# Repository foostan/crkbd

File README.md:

# Corne keyboard

The Corne keyboard is a split keyboard with 3x6 column staggered keys
and 3 thumb keys, based on [Helix](https://github.com/MakotoKurauchi/helix).
Crkbd stands for Corne Keyboard.

## Latest versions
- corne-cherry: for Cherry MX compatible switches

  - v4 Hotswappable ([JP](docs/corne-cherry/v4/buildguide_jp.md)/[EN](docs/corne-cherry/v4/buildguide_en.md))
  - v4 Soldering (will be released)
- corne-chocolate: for Kailh choc v1 and v2 switches
  - v4 Hotswappable ([JP](docs/corne-chocolate/v4/buildguide_jp.md)/[EN](docs/corne-chocolate/v4/buildguide_en.md)):
  - v4 Soldering (will be released)

## Old versions

- corne-classic: for Cherry MX compatible switches 
  - v1 Soldering: ([JP](docs/corne-classic/buildguide_jp.md)/[EN](docs/corne-classic/buildguide_en.md))
- corne-cherry: for Cherry MX compatible switches
  - v2 Hotswappable: ([JP](docs/corne-cherry/v2/buildguide_jp.md)/[EN](docs/corne-cherry/v2/buildguide_en.md))
  - v2 Hotswappable tilting version: ([tilting, JP](docs/corne-cherry/v2/buildguide_tilting_tenting_plate_jp.md)/[tilting, EN](docs/corne-cherry/v2/buildguide_tilting_tenting_plate_en.md)):
  - v3 Hotswappable: ([JP](docs/corne-cherry/v3/buildguide_jp.md)/[EN](docs/corne-cherry/v3/buildguide_en.md))
- corne-chocolate: for Kailh choc v1 switches
  - v2 Hotswappable: ([JP](docs/corne-chocolate/v2/buildguide_jp.md)/[EN](docs/corne-chocolate/v2/buildguide_en.md)):
- corne-light: for easy build with a simple PCB
  - v1 Soldering: ([JP](docs/corne-light/v1/buildguide_jp.md)/[EN](docs/corne-light/v1/buildguide_en.md)):
  - v2 Soldering: ([JP](docs/corne-light/v2/buildguide_low_edition_jp.md)/[EN](docs/corne-light/v2/buildguide_low_edition_en.md)):

## Notice
There are currently reports of a bug in v4.* caused by electromagnetic interference. Depending on the environment, one or both of the left and right keyboards may stop working. It is known that this is often caused by EMI emitted by mobile phones. If you experience this kind of problem, reconnect the USB, move the EMI-generating device (probably a mobile phone) more than 30 cm away from the keyboard, and observe the situation.

For more details, please see this issue. We look forward to receiving any new information.
https://github.com/foostan/crkbd/issues/265

## Images

### Cherry

### Chocolate

### Drawing

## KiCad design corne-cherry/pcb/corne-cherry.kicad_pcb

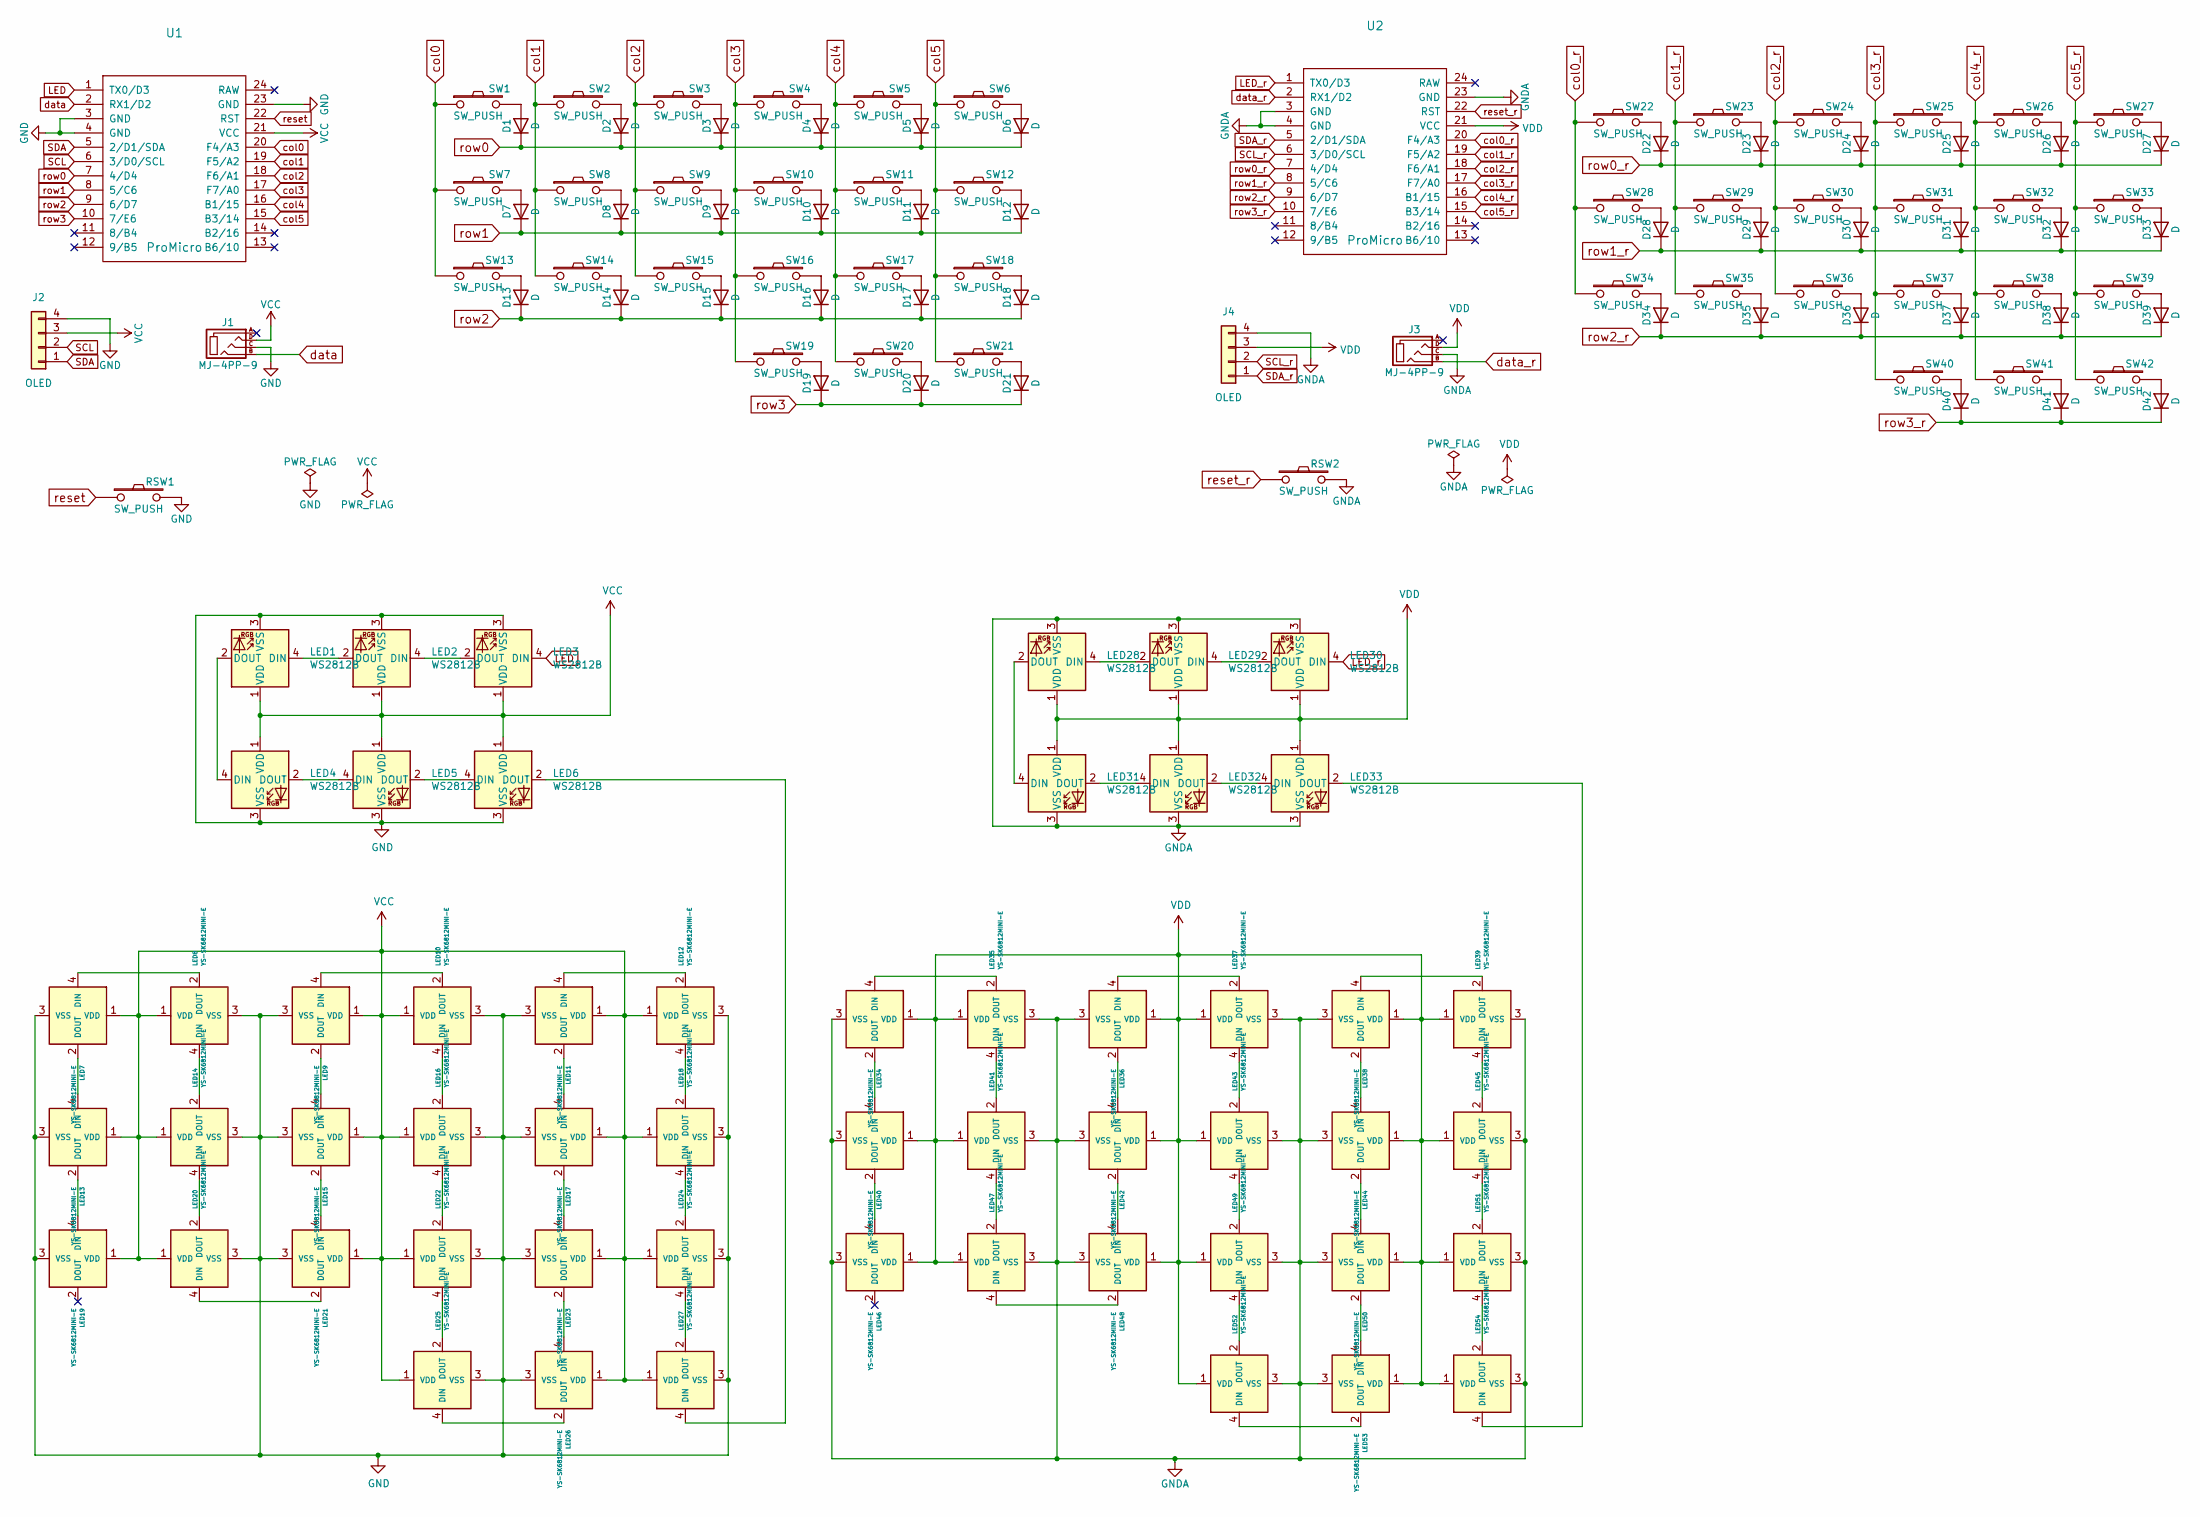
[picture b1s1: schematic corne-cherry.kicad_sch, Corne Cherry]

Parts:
D1, D2, D3, D4, D5, D6, D7, D8, D9, D10, D11, D12, D13, D14, D15, D16, D17, D18, D19, D20, D21, D22, D23, D24, D25, D26, D27, D28, D29, D30, D31, D32, D33, D34, D35, D36, D37, D38, D39, D40, D41, D42: D; D3_SMD_v2
J1, J3: MJ-4PP-9; MJ-4PP-9_1side
J2, J4: OLED; OLED_1side
LED1, LED2, LED3, LED4, LED5, LED6, LED28, LED29, LED30, LED31, LED32, LED33: WS2812B; LED_WS2812B_PLCC4_5.0x5.0mm_P3.2mm
LED7, LED8, LED9, LED10, LED11, LED12, LED13, LED14, LED15, LED16, LED17, LED18, LED19, LED20, LED21, LED22, LED23, LED24, LED25, LED26, LED27, LED34, LED35, LED36, LED37, LED38, LED39, LED40, LED41, LED42, LED43, LED44, LED45, LED46, LED47, LED48, LED49, LED50, LED51, LED52, LED53, LED54: YS-SK6812MINI-E
RSW1, RSW2: SW_PUSH; ResetSW_1side
SW1, SW2, SW3, SW4, SW5, SW6, SW7, SW8, SW9, SW10, SW11, SW12, SW13, SW14, SW15, SW16, SW17, SW18, SW19, SW20, SW22, SW23, SW24, SW25, SW26, SW27, SW28, SW29, SW30, SW31, SW32, SW33, SW34, SW35, SW36, SW37, SW38, SW39, SW40, SW41: SW_PUSH; CherryMX_Hotswap
SW21, SW42: SW_PUSH; CherryMX_Hotswap_1.5u
U1, U2: ProMicro; ProMicro_v3

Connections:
GND: J1.C, J2.4, LED1.3 (VSS), LED2.3 (VSS), LED3.3 (VSS), LED4.3 (VSS), LED5.3 (VSS), LED6.3 (VSS), LED7.3 (VSS), LED8.3 (VSS), LED9.3 (VSS), LED10.3 (VSS), LED11.3 (VSS), LED12.3 (VSS), LED13.3 (VSS), LED14.3 (VSS), LED15.3 (VSS), LED16.3 (VSS), LED17.3 (VSS), LED18.3 (VSS), LED19.3 (VSS), LED20.3 (VSS), LED21.3 (VSS), LED22.3 (VSS), LED23.3 (VSS), LED24.3 (VSS), LED25.3 (VSS), LED26.3 (VSS), LED27.3 (VSS), RSW1.2, U1.3 (GND), U1.4 (GND), U1.23 (GND)
GNDA: J3.C, J4.4, LED28.3 (VSS), LED29.3 (VSS), LED30.3 (VSS), LED31.3 (VSS), LED32.3 (VSS), LED33.3 (VSS), LED34.3 (VSS), LED35.3 (VSS), LED36.3 (VSS), LED37.3 (VSS), LED38.3 (VSS), LED39.3 (VSS), LED40.3 (VSS), LED41.3 (VSS), LED42.3 (VSS), LED43.3 (VSS), LED44.3 (VSS), LED45.3 (VSS), LED46.3 (VSS), LED47.3 (VSS), LED48.3 (VSS), LED49.3 (VSS), LED50.3 (VSS), LED51.3 (VSS), LED52.3 (VSS), LED53.3 (VSS), LED54.3 (VSS), RSW2.2, U2.3 (GND), U2.4 (GND), U2.23 (GND)
LED: LED3.4 (DIN), U1.1 (TX0/D3)
LED_r: LED30.4 (DIN), U2.1 (TX0/D3)
unnamed: D1.2 (A), SW1.2
unnamed: D2.2 (A), SW2.2
unnamed: D3.2 (A), SW3.2
unnamed: D4.2 (A), SW4.2
unnamed: D5.2 (A), SW5.2
unnamed: D6.2 (A), SW6.2
unnamed: D7.2 (A), SW7.2
unnamed: D8.2 (A), SW8.2
unnamed: D9.2 (A), SW9.2
unnamed: D10.2 (A), SW10.2
unnamed: D11.2 (A), SW11.2
unnamed: D12.2 (A), SW12.2
unnamed: D13.2 (A), SW13.2
unnamed: D14.2 (A), SW14.2
unnamed: D15.2 (A), SW15.2
unnamed: D16.2 (A), SW16.2
unnamed: D17.2 (A), SW17.2
unnamed: D18.2 (A), SW18.2
unnamed: D19.2 (A), SW19.2
unnamed: D20.2 (A), SW20.2
unnamed: D21.2 (A), SW21.2
unnamed: D22.2 (A), SW22.2
unnamed: D23.2 (A), SW23.2
unnamed: D24.2 (A), SW24.2
unnamed: D25.2 (A), SW25.2
unnamed: D26.2 (A), SW26.2
unnamed: D27.2 (A), SW27.2
unnamed: D28.2 (A), SW28.2
unnamed: D29.2 (A), SW29.2
unnamed: D30.2 (A), SW30.2
unnamed: D31.2 (A), SW31.2
unnamed: D32.2 (A), SW32.2
unnamed: D33.2 (A), SW33.2
unnamed: D34.2 (A), SW34.2
unnamed: D35.2 (A), SW35.2
unnamed: D36.2 (A), SW36.2
unnamed: D37.2 (A), SW37.2
unnamed: D38.2 (A), SW38.2
unnamed: D39.2 (A), SW39.2
unnamed: D40.2 (A), SW40.2
unnamed: D41.2 (A), SW41.2
unnamed: D42.2 (A), SW42.2
unnamed: LED1.2 (DOUT), LED4.4 (DIN)
unnamed: LED1.4 (DIN), LED2.2 (DOUT)
unnamed: LED2.4 (DIN), LED3.2 (DOUT)
unnamed: LED4.2 (DOUT), LED5.4 (DIN)
unnamed: LED5.2 (DOUT), LED6.4 (DIN)
unnamed: LED7.4 (DIN), LED8.2 (DOUT)
unnamed: LED9.4 (DIN), LED10.2 (DOUT)
unnamed: LED10.4 (DIN), LED16.2 (DOUT)
unnamed: LED11.2 (DOUT), LED17.4 (DIN)
unnamed: LED11.4 (DIN), LED12.2 (DOUT)
unnamed: LED12.4 (DIN), LED18.2 (DOUT)
unnamed: LED13.2 (DOUT), LED19.4 (DIN)
unnamed: LED7.2 (DOUT), LED13.4 (DIN)
unnamed: LED8.4 (DIN), LED14.2 (DOUT)
unnamed: LED14.4 (DIN), LED20.2 (DOUT)
unnamed: LED15.2 (DOUT), LED21.4 (DIN)
unnamed: LED9.2 (DOUT), LED15.4 (DIN)
unnamed: LED16.4 (DIN), LED22.2 (DOUT)
unnamed: LED17.2 (DOUT), LED23.4 (DIN)
unnamed: LED18.4 (DIN), LED24.2 (DOUT)
unnamed: LED20.4 (DIN), LED21.2 (DOUT)
unnamed: LED22.4 (DIN), LED25.2 (DOUT)
unnamed: LED23.2 (DOUT), LED26.4 (DIN)
unnamed: LED24.4 (DIN), LED27.2 (DOUT)
unnamed: LED25.4 (DIN), LED26.2 (DOUT)
unnamed: LED6.2 (DOUT), LED27.4 (DIN)
unnamed: LED28.2 (DOUT), LED31.4 (DIN)
unnamed: LED28.4 (DIN), LED29.2 (DOUT)
unnamed: LED29.4 (DIN), LED30.2 (DOUT)
unnamed: LED31.2 (DOUT), LED32.4 (DIN)
unnamed: LED32.2 (DOUT), LED33.4 (DIN)
unnamed: LED33.2 (DOUT), LED54.4 (DIN)
unnamed: LED34.2 (DOUT), LED40.4 (DIN)
unnamed: LED34.4 (DIN), LED35.2 (DOUT)
unnamed: LED35.4 (DIN), LED41.2 (DOUT)
unnamed: LED36.2 (DOUT), LED42.4 (DIN)
unnamed: LED36.4 (DIN), LED37.2 (DOUT)
unnamed: LED37.4 (DIN), LED43.2 (DOUT)
unnamed: LED38.2 (DOUT), LED44.4 (DIN)
unnamed: LED38.4 (DIN), LED39.2 (DOUT)
unnamed: LED39.4 (DIN), LED45.2 (DOUT)
unnamed: LED40.2 (DOUT), LED46.4 (DIN)
unnamed: LED41.4 (DIN), LED47.2 (DOUT)
unnamed: LED42.2 (DOUT), LED48.4 (DIN)
unnamed: LED43.4 (DIN), LED49.2 (DOUT)
unnamed: LED44.2 (DOUT), LED50.4 (DIN)
unnamed: LED45.4 (DIN), LED51.2 (DOUT)
unnamed: LED47.4 (DIN), LED48.2 (DOUT)
unnamed: LED49.4 (DIN), LED52.2 (DOUT)
unnamed: LED50.2 (DOUT), LED53.4 (DIN)
unnamed: LED51.4 (DIN), LED54.2 (DOUT)
unnamed: LED52.4 (DIN), LED53.2 (DOUT)
SCL: J2.2, U1.6 (3/D0/SCL)
SCL_r: J4.2, U2.6 (3/D0/SCL)
SDA: J2.1, U1.5 (2/D1/SDA)
SDA_r: J4.1, U2.5 (2/D1/SDA)
VCC: J1.D, J2.3, LED1.1 (VDD), LED2.1 (VDD), LED3.1 (VDD), LED4.1 (VDD), LED5.1 (VDD), LED6.1 (VDD), LED7.1 (VDD), LED8.1 (VDD), LED9.1 (VDD), LED10.1 (VDD), LED11.1 (VDD), LED12.1 (VDD), LED13.1 (VDD), LED14.1 (VDD), LED15.1 (VDD), LED16.1 (VDD), LED17.1 (VDD), LED18.1 (VDD), LED19.1 (VDD), LED20.1 (VDD), LED21.1 (VDD), LED22.1 (VDD), LED23.1 (VDD), LED24.1 (VDD), LED25.1 (VDD), LED26.1 (VDD), LED27.1 (VDD), U1.21 (VCC)
VDD: J3.D, J4.3, LED28.1 (VDD), LED29.1 (VDD), LED30.1 (VDD), LED31.1 (VDD), LED32.1 (VDD), LED33.1 (VDD), LED34.1 (VDD), LED35.1 (VDD), LED36.1 (VDD), LED37.1 (VDD), LED38.1 (VDD), LED39.1 (VDD), LED40.1 (VDD), LED41.1 (VDD), LED42.1 (VDD), LED43.1 (VDD), LED44.1 (VDD), LED45.1 (VDD), LED46.1 (VDD), LED47.1 (VDD), LED48.1 (VDD), LED49.1 (VDD), LED50.1 (VDD), LED51.1 (VDD), LED52.1 (VDD), LED53.1 (VDD), LED54.1 (VDD), U2.21 (VCC)
col0: SW1.1, SW7.1, SW13.1, U1.20 (F4/A3)
col0_r: SW22.1, SW28.1, SW34.1, U2.20 (F4/A3)
col1: SW2.1, SW8.1, SW14.1, U1.19 (F5/A2)
col1_r: SW23.1, SW29.1, SW35.1, U2.19 (F5/A2)
col2: SW3.1, SW9.1, SW15.1, U1.18 (F6/A1)
col2_r: SW24.1, SW30.1, SW36.1, U2.18 (F6/A1)
col3: SW4.1, SW10.1, SW16.1, SW19.1, U1.17 (F7/A0)
col3_r: SW25.1, SW31.1, SW37.1, SW40.1, U2.17 (F7/A0)
col4: SW5.1, SW11.1, SW17.1, SW20.1, U1.16 (B1/15)
col4_r: SW26.1, SW32.1, SW38.1, SW41.1, U2.16 (B1/15)
col5: SW6.1, SW12.1, SW18.1, SW21.1, U1.15 (B3/14)
col5_r: SW27.1, SW33.1, SW39.1, SW42.1, U2.15 (B3/14)
data: J1.B, U1.2 (RX1/D2)
data_r: J3.B, U2.2 (RX1/D2)
reset: RSW1.1, U1.22 (RST)
reset_r: RSW2.1, U2.22 (RST)
row0: D1.1 (K), D2.1 (K), D3.1 (K), D4.1 (K), D5.1 (K), D6.1 (K), U1.7 (4/D4)
row0_r: D22.1 (K), D23.1 (K), D24.1 (K), D25.1 (K), D26.1 (K), D27.1 (K), U2.7 (4/D4)
row1: D7.1 (K), D8.1 (K), D9.1 (K), D10.1 (K), D11.1 (K), D12.1 (K), U1.8 (5/C6)
row1_r: D28.1 (K), D29.1 (K), D30.1 (K), D31.1 (K), D32.1 (K), D33.1 (K), U2.8 (5/C6)
row2: D13.1 (K), D14.1 (K), D15.1 (K), D16.1 (K), D17.1 (K), D18.1 (K), U1.9 (6/D7)
row2_r: D34.1 (K), D35.1 (K), D36.1 (K), D37.1 (K), D38.1 (K), D39.1 (K), U2.9 (6/D7)
row3: D19.1 (K), D20.1 (K), D21.1 (K), U1.10 (7/E6)
row3_r: D40.1 (K), D41.1 (K), D42.1 (K), U2.10 (7/E6)

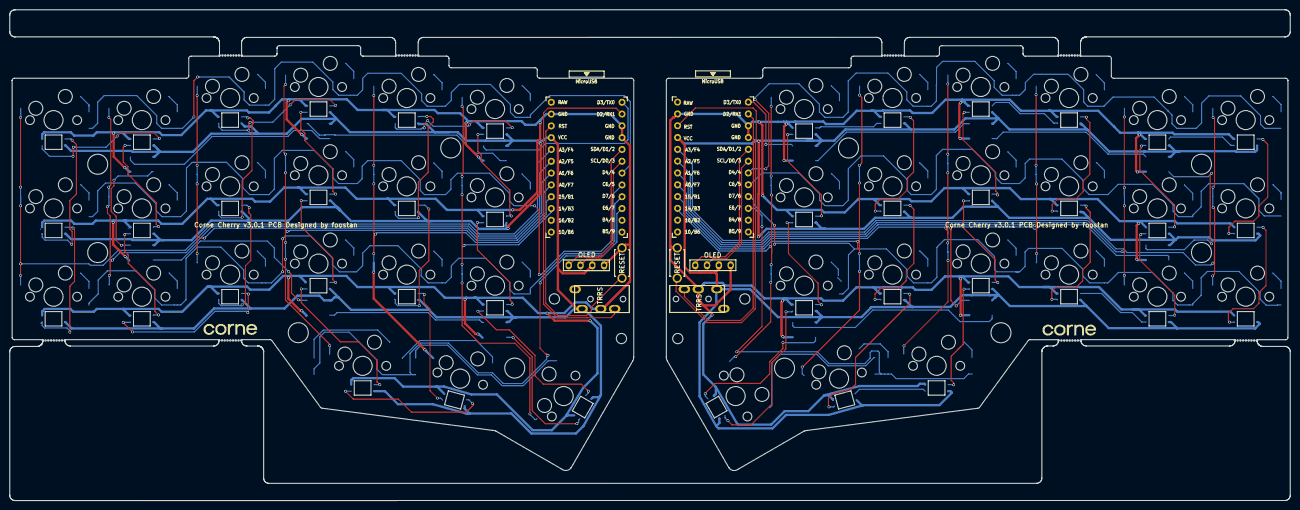
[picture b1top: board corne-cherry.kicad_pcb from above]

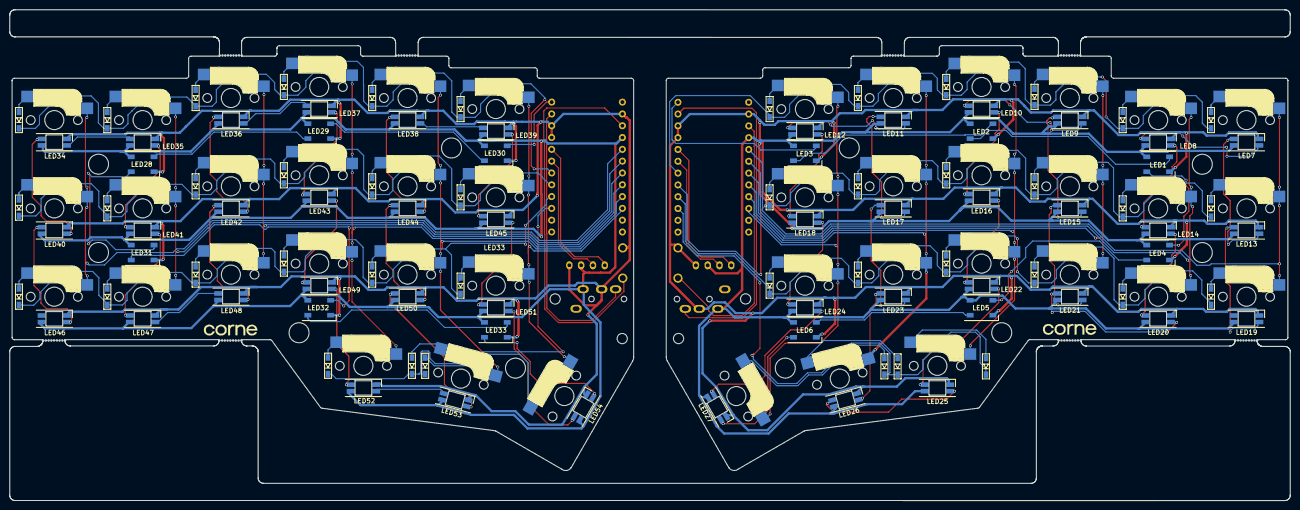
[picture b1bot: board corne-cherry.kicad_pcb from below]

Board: 2 copper layers, 275.5 x 105.6 mm, 160 parts (99 on the bottom side), 128 nets.

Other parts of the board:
Ref**: Val**; M2_HOLE_v2
Ref**#2, Ref**#3, Ref**#4, Ref**#5, Ref**#6, Ref**#7, Ref**#8, Ref**#9, Ref**#10, Ref**#11, Ref**#12, Ref**#13, Ref**#14: Val**; M2_HOLE_v2

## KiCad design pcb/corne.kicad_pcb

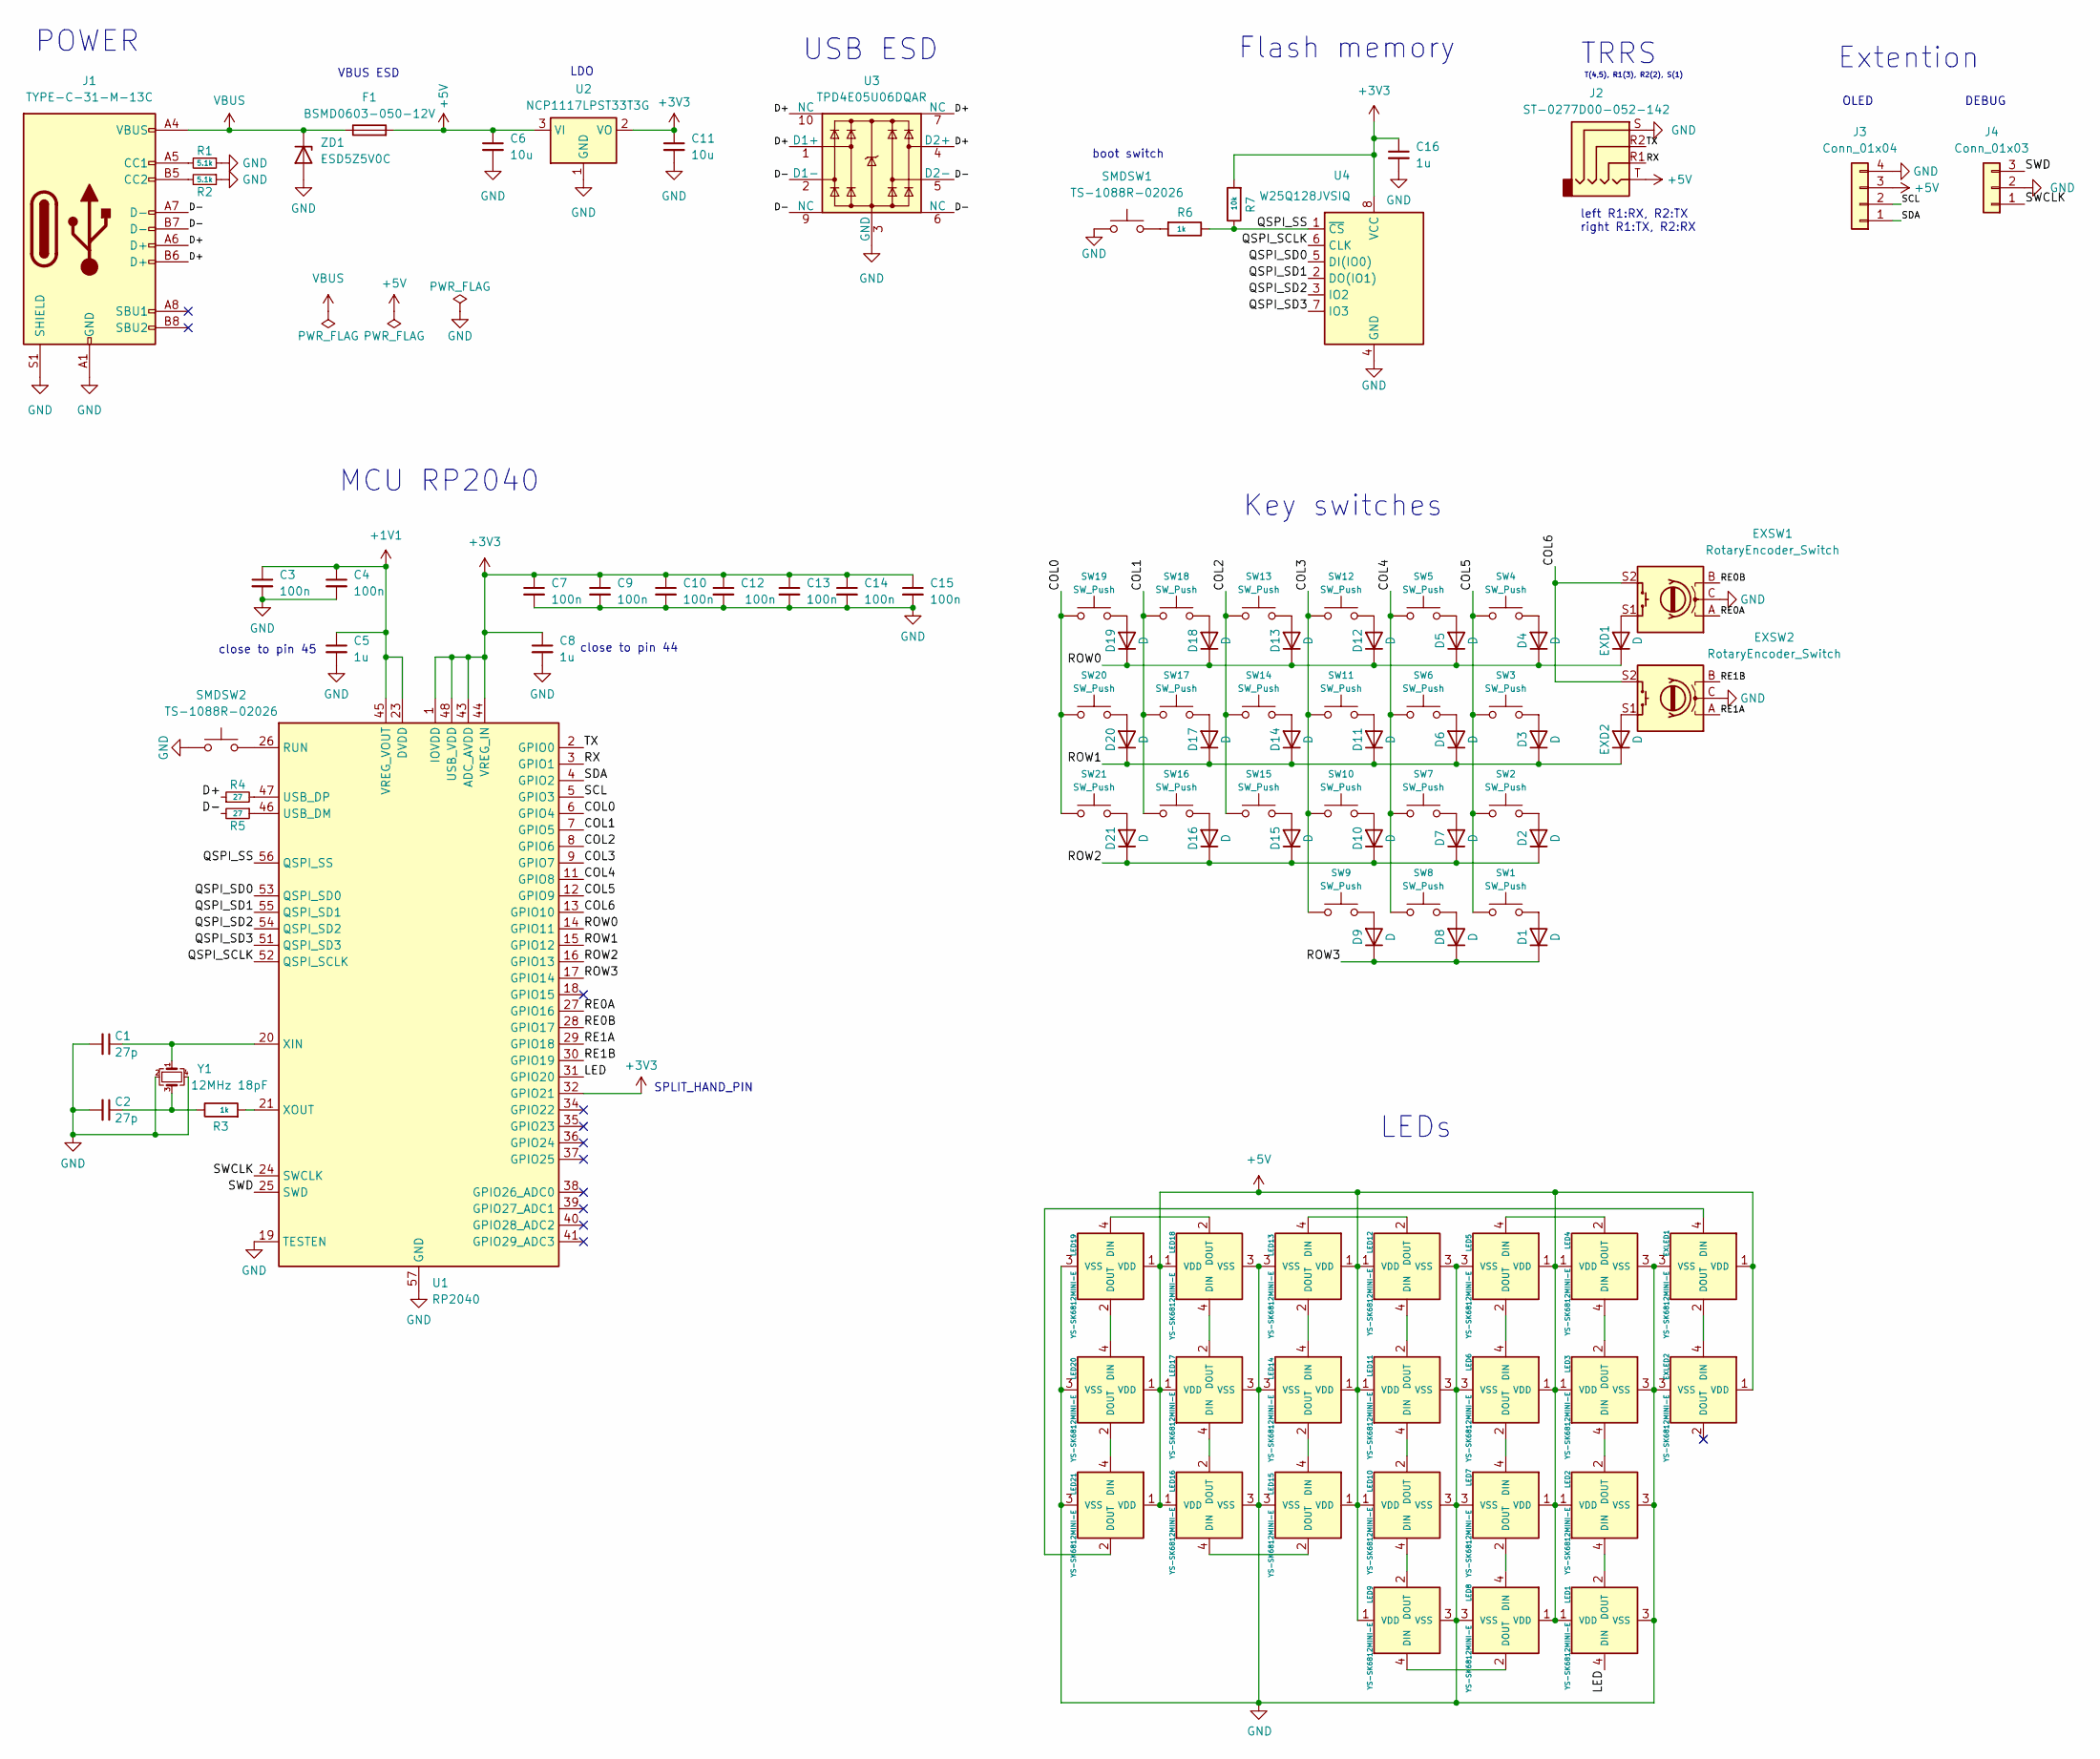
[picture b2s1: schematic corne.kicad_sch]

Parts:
C1, C2: 27p; C_0402_1005Metric
C3, C4, C7, C9, C10, C12, C13, C14, C15: 100n; C_0402_1005Metric
C5, C8, C16: 1u; C_0402_1005Metric
C6, C11: 10u; C_0402_1005Metric
D1, D2, D3, D4, D5, D6, D7, D8, D9, D10, D11, D12, D13, D14, D15, D16, D17, D18, D19, D20, D21: D; D_0603_1608Metric
EXD1, EXD2: D; D_0603_1608Metric
EXLED1, EXLED2: YS-SK6812MINI-E
EXSW1, EXSW2: RotaryEncoder_Switch; keyswitch_cherrymx_hotswap_1u_rotary_encoder_ec12
F1: BSMD0603-050-12V; Fuse_0603_1608Metric; JLCPCB Part # C2844464
J1: TYPE-C-31-M-13C; JLCPCB Part # C2848620
J2: ST-0277D00-052-142; JLCPCB Part # C2837093
J3: Conn_01x04; OLED
J4: Conn_01x03; PinHeader_1x03_P2.54mm_Vertical
LED1, LED2, LED3, LED4, LED5, LED6, LED7, LED8, LED9, LED10, LED11, LED12, LED13, LED14, LED15, LED16, LED17, LED18, LED19, LED20, LED21: YS-SK6812MINI-E
R1, R2: 5.1k; R_0603_1608Metric
R3, R6: 1k; R_0603_1608Metric
R4, R5: 27; R_0603_1608Metric
R7: 10k; R_0603_1608Metric
SMDSW1, SMDSW2: TS-1088R-02026; JLCPCB Part # C455280
SW1: SW_Push; keyswitch_cherrymx_hotswap_1.5u
SW2, SW3, SW4, SW5, SW6, SW7, SW8, SW9, SW10, SW11, SW12, SW13, SW14, SW15, SW16, SW17, SW18, SW19, SW20, SW21: SW_Push; keyswitch_cherrymx_hotswap_1u
U1: RP2040; QFN-56-1EP_7x7mm_P0.4mm_EP3.2x3.2mm; JLCPCB Part # C2040
U2: NCP1117LPST33T3G; SOT-223-3_TabPin2; JLCPCB Part # C146799
U3: TPD4E05U06DQAR; USON-10_2.5x1.0mm_P0.5mm; JLCPCB Part # C138714
U4: W25Q128JVSIQ; SOIC-8_5.23x5.23mm_P1.27mm; JLCPCB Part # C113767
Y1: 12MHz 18pF; Crystal_SMD_3225-4Pin_3.2x2.5mm; MFR.Part # Q22FA23V0041800; JLCPCB Part # C91749
ZD1: ESD5Z5V0C; D_SOD-523; JLCPCB Part # C2901325

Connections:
+1V1: C3.1, C4.1, C5.1, U1.23 (DVDD), U1.45 (VREG_VOUT), U1.50 (DVDD)
+3V3: C7.1, C8.1, C9.1, C10.1, C11.1, C12.1, C13.1, C14.1, C15.1, C16.1, R7.2, U1.1 (IOVDD), U1.10 (IOVDD), U1.22 (IOVDD), U1.32 (GPIO21), U1.33 (IOVDD), U1.42 (IOVDD), U1.43 (ADC_AVDD), U1.44 (VREG_IN), U1.48 (USB_VDD), U1.49 (IOVDD), U2.2 (VO), U4.8 (VCC)
+5V: C6.1, EXLED1.1 (VDD), EXLED2.1 (VDD), F1.2, J2.T, J3.3, LED1.1 (VDD), LED2.1 (VDD), LED3.1 (VDD), LED4.1 (VDD), LED5.1 (VDD), LED6.1 (VDD), LED7.1 (VDD), LED8.1 (VDD), LED9.1 (VDD), LED10.1 (VDD), LED11.1 (VDD), LED12.1 (VDD), LED13.1 (VDD), LED14.1 (VDD), LED15.1 (VDD), LED16.1 (VDD), LED17.1 (VDD), LED18.1 (VDD), LED19.1 (VDD), LED20.1 (VDD), LED21.1 (VDD), U2.3 (VI)
/COL0: SW19.1, SW20.1, SW21.1, U1.6 (GPIO4)
/COL1: SW16.1, SW17.1, SW18.1, U1.7 (GPIO5)
/COL2: SW13.1, SW14.1, SW15.1, U1.8 (GPIO6)
/COL3: SW9.1, SW10.1, SW11.1, SW12.1, U1.9 (GPIO7)
/COL4: SW5.1, SW6.1, SW7.1, SW8.1, U1.11 (GPIO8)
/COL5: SW1.1, SW2.1, SW3.1, SW4.1, U1.12 (GPIO9)
/COL6: EXSW1.S2, EXSW2.S2, U1.13 (GPIO10)
/D+: J1.A6 (D+), J1.B6 (D+), R4.1, U3.1 (D1+), U3.4 (D2+), U3.7 (NC), U3.10 (NC)
/D-: J1.A7 (D-), J1.B7 (D-), R5.2, U3.2 (D1-), U3.5 (D2-), U3.6 (NC), U3.9 (NC)
/LED: LED1.4 (DIN), U1.31 (GPIO20)
/QSPI_SCLK: U1.52 (QSPI_SCLK), U4.6 (CLK)
/QSPI_SD0: U1.53 (QSPI_SD0), U4.5 (DI(IO0))
/QSPI_SD1: U1.55 (QSPI_SD1), U4.2 (DO(IO1))
/QSPI_SD2: U1.54 (QSPI_SD2), U4.3 (IO2)
/QSPI_SD3: U1.51 (QSPI_SD3), U4.7 (IO3)
/QSPI_SS: R6.1, R7.1, U1.56 (QSPI_SS), U4.1 (~CS)
/RE0A: EXSW1.A, U1.27 (GPIO16)
/RE0B: EXSW1.B, U1.28 (GPIO17)
/RE1A: EXSW2.A, U1.29 (GPIO18)
/RE1B: EXSW2.B, U1.30 (GPIO19)
/ROW0: D4.1 (K), D5.1 (K), D12.1 (K), D13.1 (K), D18.1 (K), D19.1 (K), EXD1.1 (K), U1.14 (GPIO11)
/ROW1: D3.1 (K), D6.1 (K), D11.1 (K), D14.1 (K), D17.1 (K), D20.1 (K), EXD2.1 (K), U1.15 (GPIO12)
/ROW2: D2.1 (K), D7.1 (K), D10.1 (K), D15.1 (K), D16.1 (K), D21.1 (K), U1.16 (GPIO13)
/ROW3: D1.1 (K), D8.1 (K), D9.1 (K), U1.17 (GPIO14)
/RX: J2.R1, U1.3 (GPIO1)
/SCL: J3.2, U1.5 (GPIO3)
/SDA: J3.1, U1.4 (GPIO2)
/SWCLK: J4.1, U1.24 (SWCLK)
/SWD: J4.3, U1.25 (SWD)
/TX: J2.R2, U1.2 (GPIO0)
GND: C1.2, C2.2, C3.2, C4.2, C5.2, C6.2, C7.2, C8.2, C9.2, C10.2, C11.2, C12.2, C13.2, C14.2, C15.2, C16.2, EXLED1.3 (VSS), EXLED2.3 (VSS), EXSW1.C, EXSW2.C, J1.A1 (GND), J1.A12 (GND), J1.B1 (GND), J1.B12 (GND), J1.S1 (SHIELD), J2.S, J3.4, J4.2, LED1.3 (VSS), LED2.3 (VSS), LED3.3 (VSS), LED4.3 (VSS), LED5.3 (VSS), LED6.3 (VSS), LED7.3 (VSS), LED8.3 (VSS), LED9.3 (VSS), LED10.3 (VSS), LED11.3 (VSS), LED12.3 (VSS), LED13.3 (VSS), LED14.3 (VSS), LED15.3 (VSS), LED16.3 (VSS), LED17.3 (VSS), LED18.3 (VSS), LED19.3 (VSS), LED20.3 (VSS), LED21.3 (VSS), R1.1, R2.1, SMDSW1.1, SMDSW2.1, U1.19 (TESTEN), U1.57 (GND), U2.1 (GND), U3.3 (GND), U3.8 (GND), U4.4 (GND), Y1.2, Y1.4, ZD1.2 (A)
unnamed: C2.1, R3.1, Y1.3
unnamed: D1.2 (A), SW1.2
unnamed: D2.2 (A), SW2.2
unnamed: D3.2 (A), SW3.2
unnamed: D4.2 (A), SW4.2
unnamed: D5.2 (A), SW5.2
unnamed: D6.2 (A), SW6.2
unnamed: D7.2 (A), SW7.2
unnamed: D8.2 (A), SW8.2
unnamed: D9.2 (A), SW9.2
unnamed: D10.2 (A), SW10.2
unnamed: D11.2 (A), SW11.2
unnamed: D12.2 (A), SW12.2
unnamed: D13.2 (A), SW13.2
unnamed: D14.2 (A), SW14.2
unnamed: D15.2 (A), SW15.2
unnamed: D16.2 (A), SW16.2
unnamed: D17.2 (A), SW17.2
unnamed: D18.2 (A), SW18.2
unnamed: D19.2 (A), SW19.2
unnamed: D20.2 (A), SW20.2
unnamed: D21.2 (A), SW21.2
unnamed: EXD1.2 (A), EXSW1.S1
unnamed: EXD2.2 (A), EXSW2.S1
unnamed: EXLED1.4 (DIN), LED21.2 (DOUT)
unnamed: EXLED1.2 (DOUT), EXLED2.4 (DIN)
unnamed: J1.A5 (CC1), R1.2
unnamed: J1.B5 (CC2), R2.2
unnamed: LED1.2 (DOUT), LED2.4 (DIN)
unnamed: LED2.2 (DOUT), LED3.4 (DIN)
unnamed: LED3.2 (DOUT), LED4.4 (DIN)
unnamed: LED4.2 (DOUT), LED5.4 (DIN)
unnamed: LED5.2 (DOUT), LED6.4 (DIN)
unnamed: LED6.2 (DOUT), LED7.4 (DIN)
unnamed: LED7.2 (DOUT), LED8.4 (DIN)
unnamed: LED8.2 (DOUT), LED9.4 (DIN)
unnamed: LED9.2 (DOUT), LED10.4 (DIN)
unnamed: LED10.2 (DOUT), LED11.4 (DIN)
unnamed: LED11.2 (DOUT), LED12.4 (DIN)
unnamed: LED12.2 (DOUT), LED13.4 (DIN)
unnamed: LED13.2 (DOUT), LED14.4 (DIN)
unnamed: LED14.2 (DOUT), LED15.4 (DIN)
unnamed: LED15.2 (DOUT), LED16.4 (DIN)
unnamed: LED16.2 (DOUT), LED17.4 (DIN)
unnamed: LED17.2 (DOUT), LED18.4 (DIN)
unnamed: LED18.2 (DOUT), LED19.4 (DIN)
unnamed: LED19.2 (DOUT), LED20.4 (DIN)
unnamed: LED20.2 (DOUT), LED21.4 (DIN)
unnamed: R6.2, SMDSW1.2
unnamed: SMDSW2.2, U1.26 (RUN)
unnamed: R5.1, U1.46 (USB_DM)
unnamed: R4.2, U1.47 (USB_DP)
unnamed: C1.1, U1.20 (XIN), Y1.1
unnamed: R3.2, U1.21 (XOUT)
VBUS: F1.1, J1.A4 (VBUS), J1.A9 (VBUS), J1.B4 (VBUS), J1.B9 (VBUS), ZD1.1 (K)

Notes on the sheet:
TRRS
left R1:RX, R2:TX right R1:TX, R2:RX
POWER
close to pin 44
T(4,5), R1(3), R2(2), S(1)
LDO
USB ESD
boot switch
DEBUG
Key switches
SPLIT_HAND_PIN
Flash memory
close to pin 45
Extention
LEDs
MCU RP2040
VBUS ESD
OLED

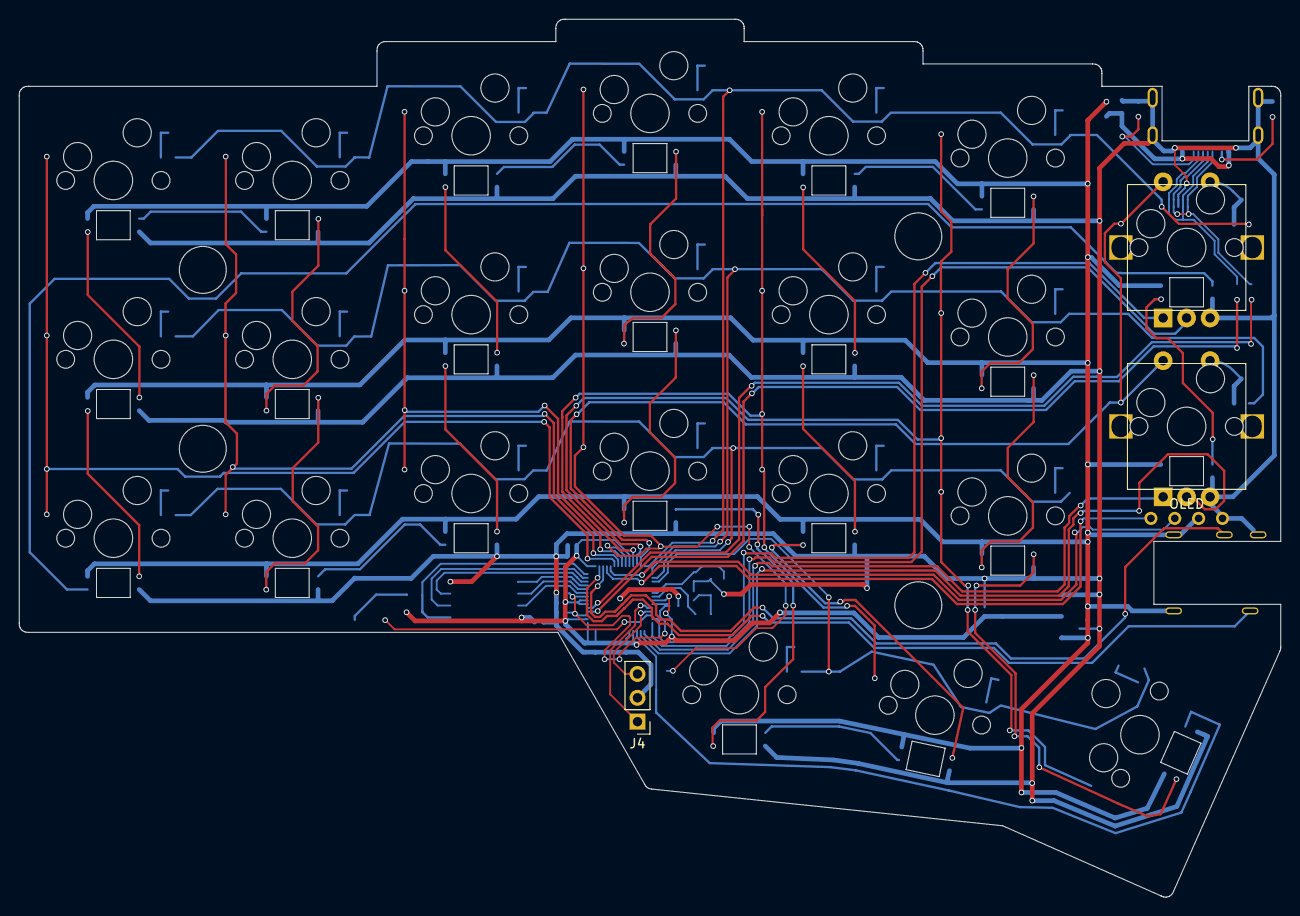
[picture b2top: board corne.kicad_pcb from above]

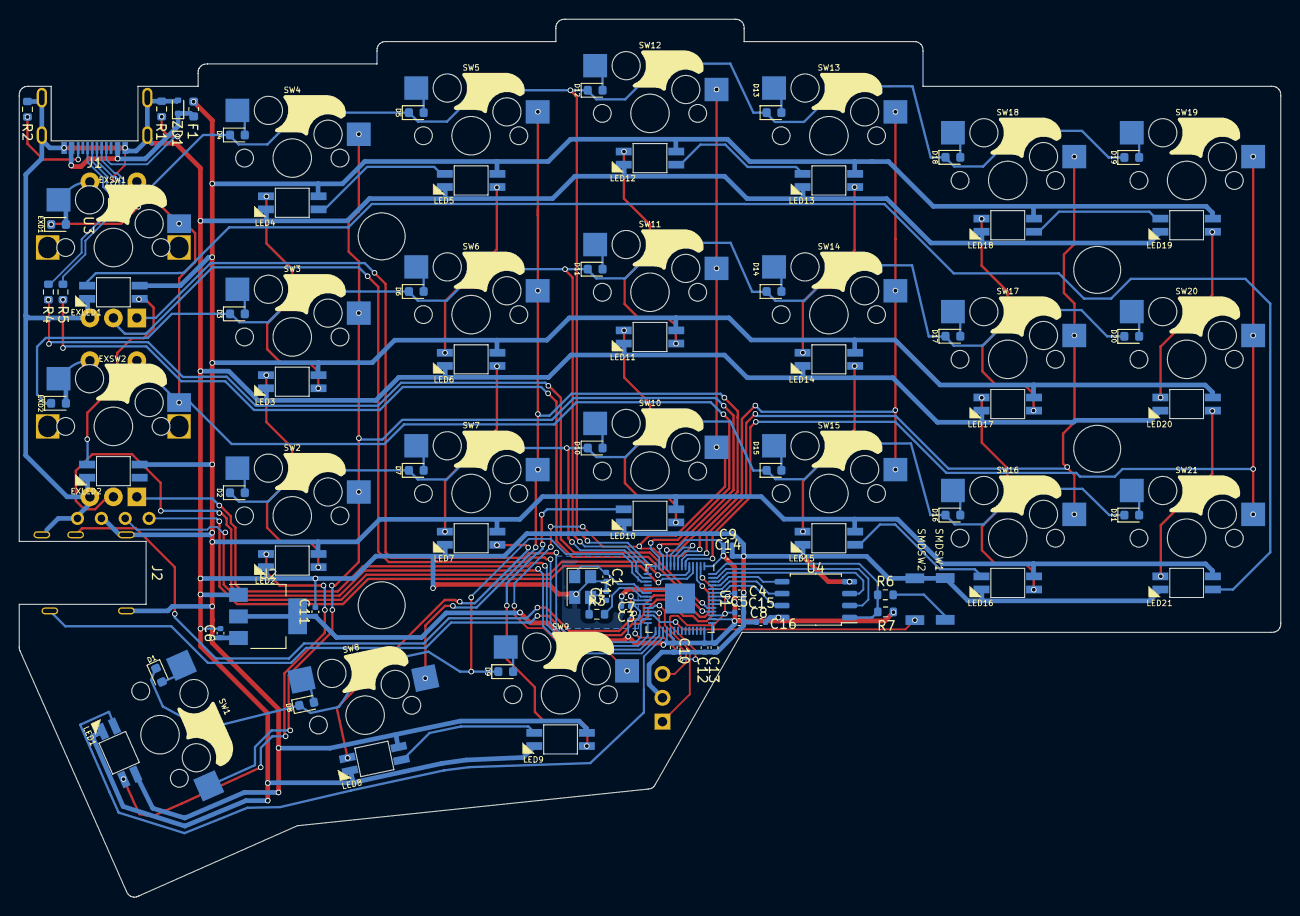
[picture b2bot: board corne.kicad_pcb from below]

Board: 2 copper layers, 134.3 x 93.5 mm, 105 parts (80 on the bottom side), 89 nets.

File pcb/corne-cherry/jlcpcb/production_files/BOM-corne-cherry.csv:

Comment,Designator,Footprint,LCSC
W25Q128JVSIQ,"U4,rU4",SOIC-8_5.23x5.23mm_P1.27mm,C113767
1k,"R3,R6,rR3,rR6",R_0402_1005Metric,C11702
TPD4E05U06DQAR,"U3,rU3",USON-10_2.5x1.0mm_P0.5mm,C138714
NCP1117LPST33T3G,"U2,rU2",SOT-223-3_TabPin2,C146799
100n,"C10,C12,C13,C14,C15,C3,C4,C7,C9,rC10,rC12,rC13,rC14,rC15,rC3,rC4,rC7,rC9",C_0402_1005Metric,C1525
10u,"C11,C6,rC11,rC6",C_0402_1005Metric,C15525
27p,"C1,C2,rC1,rC2",C_0402_1005Metric,C1557
RP2040,"U1,rU1",QFN-56-1EP_7x7mm_P0.4mm_EP3.2x3.2mm,C2040
1N4148WT,"D1,rD1",D_SOD-523,C232841
10k,"R7,rR7",R_0402_1005Metric,C25744
5.1k,"R1,R2,rR1,rR2",R_0402_1005Metric,C25905
ST-0277D00-052-142,"J2,rJ2",ST-0277D00-052-142,C2837093
BSMD0603-050-12V,"F1,rF1",Fuse_0603_1608Metric,C2844464
TYPE-C-31-M-13C,"J1,rJ1",TYPE-C-31-M-13C,C2848620
ESD5Z5V0C,"ZD1,rZD1",D_SOD-523,C2901325
27,"R4,R5,rR4,rR5",R_0402_1005Metric,C2909343
TS-1088R-02026,"SMDSW1,SMDSW2,rSMDSW1,rSMDSW2",TS-1088R-02026,C455280
RotaryEncoder_Switch,"EXSW1,EXSW2,SW1,SW10,SW11,SW12,SW13,SW14,SW15,SW16,SW17,SW18,SW19,SW2,SW20,SW21,SW3,SW4,SW5,SW6,SW7,SW8,SW9,rEXSW1,rEXSW2,rSW1,rSW10,rSW11,rSW12,rSW13,rSW14,rSW15,rSW16,rSW17,rSW18,rSW19,rSW2,rSW20,rSW21,rSW3,rSW4,rSW5,rSW6,rSW7,rSW8,rSW9",keyswitch_cherrymx_hotswap_1u_rotary_encoder_ec12,C5156480
1u,"C16,C5,C8,rC16,rC5,rC8",C_0402_1005Metric,C52923
12MHz 18pF,"Y1,rY1",Crystal_SMD_3225-4Pin_3.2x2.5mm,C91749
YS-SK6812MINI-E,LED16,YS-SK6812MINI-E,C5149201
YS-SK6812MINI-E,rLED16,YS-SK6812MINI-E,C5149201
YS-SK6812MINI-E,LED3,YS-SK6812MINI-E,C5149201
YS-SK6812MINI-E,rLED4,YS-SK6812MINI-E,C5149201
YS-SK6812MINI-E,LED17,YS-SK6812MINI-E,C5149201
YS-SK6812MINI-E,rLED6,YS-SK6812MINI-E,C5149201
YS-SK6812MINI-E,LED5,YS-SK6812MINI-E,C5149201
YS-SK6812MINI-E,rLED2,YS-SK6812MINI-E,C5149201
YS-SK6812MINI-E,LED8,YS-SK6812MINI-E,C5149201
YS-SK6812MINI-E,LED10,YS-SK6812MINI-E,C5149201
YS-SK6812MINI-E,rLED20,YS-SK6812MINI-E,C5149201
YS-SK6812MINI-E,LED12,YS-SK6812MINI-E,C5149201
YS-SK6812MINI-E,rLED15,YS-SK6812MINI-E,C5149201
YS-SK6812MINI-E,LED20,YS-SK6812MINI-E,C5149201
YS-SK6812MINI-E,rEXLED1,YS-SK6812MINI-E,C5149201
YS-SK6812MINI-E,rLED17,YS-SK6812MINI-E,C5149201
YS-SK6812MINI-E,rLED19,YS-SK6812MINI-E,C5149201
YS-SK6812MINI-E,LED15,YS-SK6812MINI-E,C5149201
YS-SK6812MINI-E,LED1,YS-SK6812MINI-E,C5149201
YS-SK6812MINI-E,rLED5,YS-SK6812MINI-E,C5149201
YS-SK6812MINI-E,rLED8,YS-SK6812MINI-E,C5149201
YS-SK6812MINI-E,rLED13,YS-SK6812MINI-E,C5149201
YS-SK6812MINI-E,LED13,YS-SK6812MINI-E,C5149201
YS-SK6812MINI-E,LED21,YS-SK6812MINI-E,C5149201
YS-SK6812MINI-E,LED19,YS-SK6812MINI-E,C5149201
YS-SK6812MINI-E,LED7,YS-SK6812MINI-E,C5149201
YS-SK6812MINI-E,rLED14,YS-SK6812MINI-E,C5149201
YS-SK6812MINI-E,rLED9,YS-SK6812MINI-E,C5149201
YS-SK6812MINI-E,EXLED2,YS-SK6812MINI-E,C5149201
YS-SK6812MINI-E,LED9,YS-SK6812MINI-E,C5149201
YS-SK6812MINI-E,EXLED1,YS-SK6812MINI-E,C5149201
YS-SK6812MINI-E,LED6,YS-SK6812MINI-E,C5149201
YS-SK6812MINI-E,rLED10,YS-SK6812MINI-E,C5149201
YS-SK6812MINI-E,rLED12,YS-SK6812MINI-E,C5149201
YS-SK6812MINI-E,rLED11,YS-SK6812MINI-E,C5149201
YS-SK6812MINI-E,rLED21,YS-SK6812MINI-E,C5149201
YS-SK6812MINI-E,rLED3,YS-SK6812MINI-E,C5149201
YS-SK6812MINI-E,LED11,YS-SK6812MINI-E,C5149201
YS-SK6812MINI-E,rEXLED2,YS-SK6812MINI-E,C5149201
YS-SK6812MINI-E,LED2,YS-SK6812MINI-E,C5149201
YS-SK6812MINI-E,LED14,YS-SK6812MINI-E,C5149201
YS-SK6812MINI-E,rLED1,YS-SK6812MINI-E,C5149201
YS-SK6812MINI-E,LED18,YS-SK6812MINI-E,C5149201
YS-SK6812MINI-E,LED4,YS-SK6812MINI-E,C5149201
YS-SK6812MINI-E,rLED7,YS-SK6812MINI-E,C5149201
YS-SK6812MINI-E,rLED18,YS-SK6812MINI-E,C5149201
